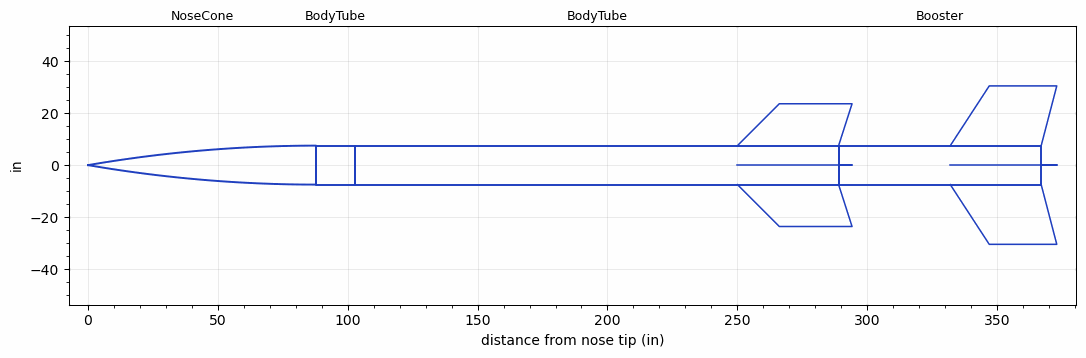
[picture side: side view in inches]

<RASAeroDocument>
 <FileVersion>2</FileVersion>
 <RocketDesign>
  <NoseCone>
   <Length>87.8</Length>
   <Diameter>15</Diameter>
   <Shape>Tangent Ogive</Shape>
   <Location>0</Location>
  </NoseCone>
  <BodyTube>
   <Length>15</Length>
   <Diameter>15</Diameter>
   <Location>87.8</Location>
  </BodyTube>
  <BodyTube>
   <Length>186.2</Length>
   <Diameter>15</Diameter>
   <Location>102.8</Location>
   <Fin>
    <Count>4</Count>
    <Chord>38.96</Chord>
    <Span>16.13</Span>
    <SweepDistance>16.13</SweepDistance>
    <TipChord>28</TipChord>
    <Thickness>1.1</Thickness>
    <Location>38.96</Location>
    <AirfoilSection>Hexagonal Blunt Base</AirfoilSection>
    <FX1>6</FX1>
   </Fin>
  </BodyTube>
  <Booster>
   <Length>78</Length>
   <Diameter>15</Diameter>
   <InsideDiameter>15</InsideDiameter>
   <Location>289</Location>
   <ShoulderLength>0</ShoulderLength>
   <Fin>
    <Count>4</Count>
    <Chord>35</Chord>
    <Span>23</Span>
    <SweepDistance>15</SweepDistance>
    <TipChord>26</TipChord>
    <Thickness>1.1</Thickness>
    <Location>35</Location>
    <AirfoilSection>Hexagonal Blunt Base</AirfoilSection>
    <FX1>6</FX1>
   </Fin>
  </Booster>
  <Surface>Sheet Metal</Surface>
  <ModifiedBarrowman>True</ModifiedBarrowman>
  <Turbulence>False</Turbulence>
  <UseBooster1>False</UseBooster1>
  <UseBooster2>False</UseBooster2>
  <Comments>Aerobee 150A

1960-1980's sounding rocket used by NASA. Built by the Aerojet-General Corperation, orginally for the Navy under the direction of the APL and NRL.</Comments>
 </RocketDesign>
 <LaunchSite>
  <Altitude>4000</Altitude>
  <Pressure>0</Pressure>
  <RodAngle>0.5</RodAngle>
  <RodLength>12</RodLength>
  <Temperature>85</Temperature>
  <WindSpeed>3</WindSpeed>
 </LaunchSite>
 <Recovery>
  <Altitude1>1000</Altitude1>
  <Altitude2>1000</Altitude2>
  <DeviceType1>None</DeviceType1>
  <DeviceType2>None</DeviceType2>
  <Event1>False</Event1>
  <Event2>False</Event2>
  <Size1>1</Size1>
  <Size2>1</Size2>
  <EventType1>None</EventType1>
  <EventType2>None</EventType2>
  <CD1>1.33</CD1>
  <CD2>1.33</CD2>
 </Recovery>
</RASAeroDocument>
